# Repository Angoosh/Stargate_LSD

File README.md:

# Stargate_LSD
A Stargate Atlantis lifesigns detector prop design files and software. This is not a 1:1 prop replica, because I couldn't find screen which would match, but it is close enough. It was originally made as a reaction to one of my friends suggestions that we need a dork particle detector or as in our czech language kokoton detektor.

## Case printing and painting:
Case is printed out on a Elegoo Mars 2 Pro resin printer with Phrozen aqua clear resin. Painting is done with diluted transparent blue enamel paint and sanded over.

## Electronics:
Mainboard: [[https://github.com/LaskaKit/ESPD-35/tree/main]] but anything should fit with 3d model change. It is based on ESP32 because I wanted simplicity of arduino and wireless capabilities for future functions.<br>
Buttons use my custom PCB made with KiCAD.<br>
For sensors: SHT40 and VL53L0X are used.<br>
Optional other sensors and stuff can be programmed in and connected via pin header in the bottom of the device.

## Software:
It is a mess made on long nights over a 4 month period. It contains 3 modes in which it can operate:<br>
Dork particle detector, which uses the ToF sensor.<br
A temperature and humidity monitor.<br>
And as a life signs detector which is WIP and I don't know when it will be finished with all features. Right now it is just a simple blinking and beeping dot in the middle of the screen, but I have an idea to make it into a "real" life signs detector with an array of stationary beacons scattered around an area where it should detect stuff which will triangulate positions of the LSD and other mobile beacons and send that data into the LSD over MQTT or something like that. I don't know when I will have the time and mood to do that. Probably when the need arises for some LARP or something.

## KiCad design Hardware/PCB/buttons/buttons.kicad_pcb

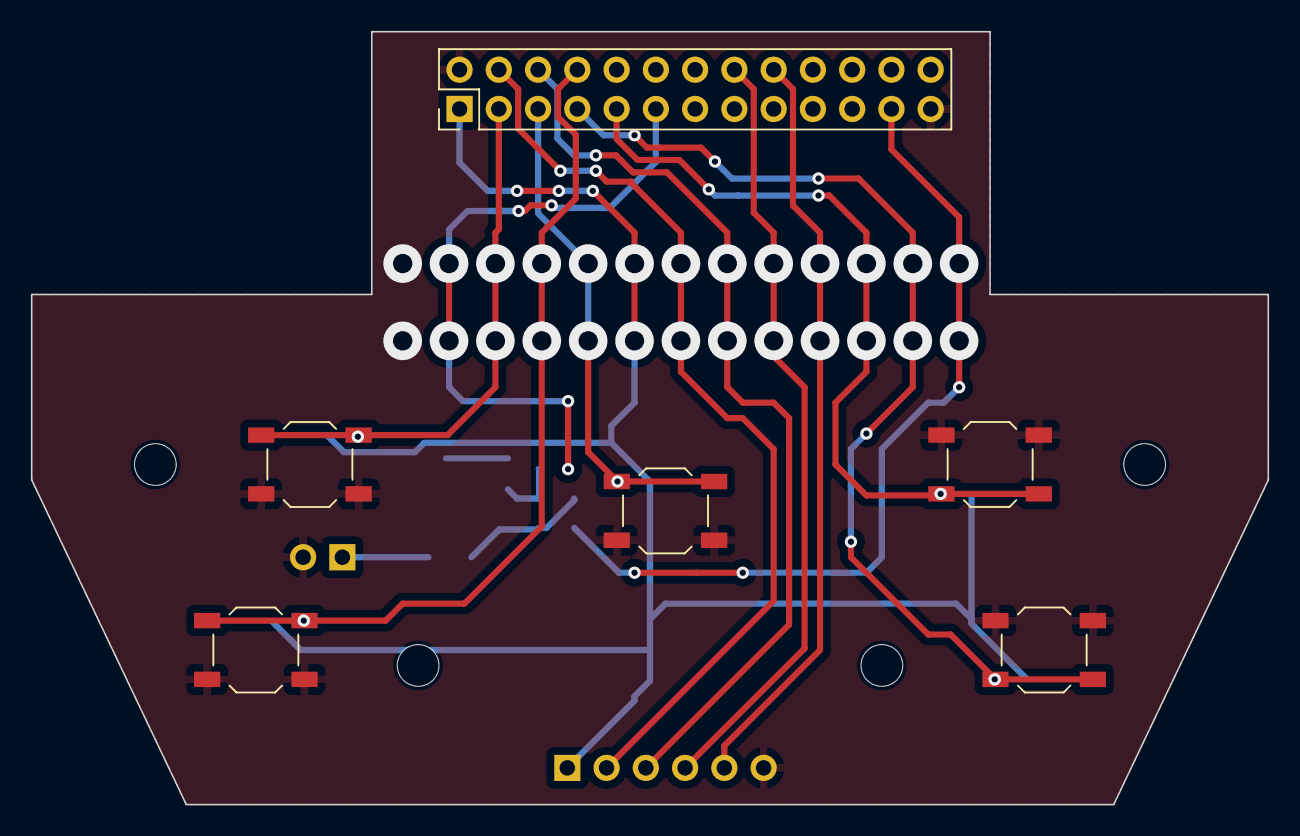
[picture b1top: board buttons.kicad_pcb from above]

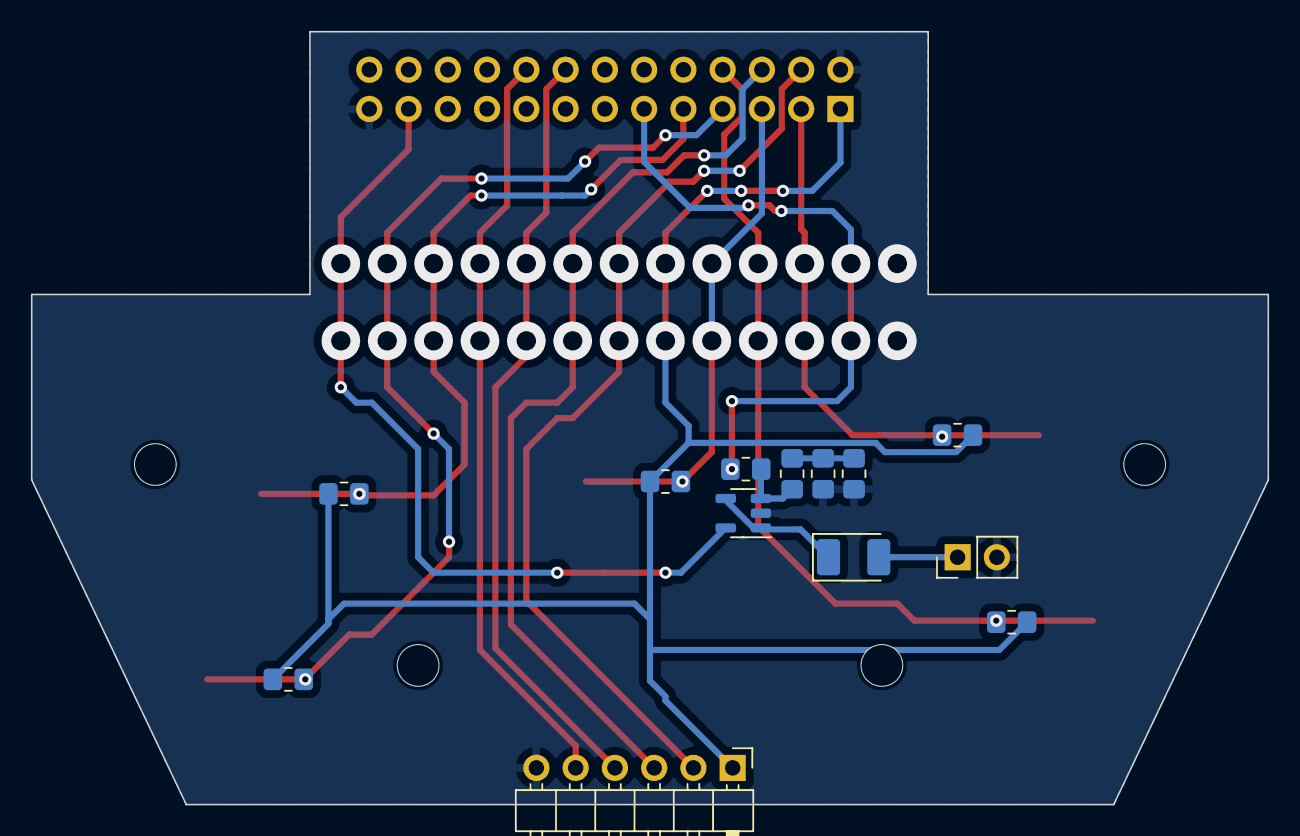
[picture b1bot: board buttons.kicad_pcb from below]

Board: 2 copper layers, 80.0 x 50.0 mm, 19 parts (13 on the bottom side), 17 nets.

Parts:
C1: 47u; CP_EIA-3528-21_Kemet-B_Pad1.50x2.35mm_HandSolder
J1: Conn_02x13_Odd_Even; PinHeader_2x13_P2.54mm_Vertical
J2: Conn_01x06; PinHeader_1x06_P2.54mm_Horizontal
LS1: Speaker; PinHeader_1x02_P2.54mm_Vertical
R1, R2, R3, R4: 10k; R_0805_2012Metric_Pad1.20x1.40mm_HandSolder
R5, R6, R7, R8, R9: 4k7; R_0805_2012Metric_Pad1.20x1.40mm_HandSolder
SW1, SW2, SW3, SW4, SW5: SW_Push; SW_SPST_TL3342
U1: AD8531ARTZ; SOT-23-5

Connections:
+3V3: J1.1, J2.1, R5.1, R6.1, R7.1, R8.1, R9.1
+BATT: J1.23, U1.5 (V+)
/SCL: J1.18, J2.5
/SDA: J1.16, J2.4
/SOUND: J1.11, R1.2
/SW_BACK: J1.7, R9.2, SW5.2
/SW_CENT: J1.5, R7.2, SW3.1
/SW_DWN: J1.8, R5.2, SW2.1
/SW_MENU: J1.9, R8.2, SW4.2
/SW_RX: J1.4, J2.2
/SW_TX: J1.6, J2.3
/SW_UP: J1.3, R6.2, SW1.1
GND: J1.2, J1.25, J2.6, LS1.2, R3.2, R4.2, SW1.2, SW2.2, SW3.2, SW4.1, SW5.1, U1.2 (V-)
unnamed: C1.2, LS1.1
unnamed: R2.2, R3.1, R4.1
unnamed: R1.1, R2.1, U1.3 (+)
unnamed: C1.1, U1.1, U1.4 (-)

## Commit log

2024-01-01 initial batch commit
2024-01-01 hardware, function and software description added to readme and kicad files aded
2024-01-01 image added
